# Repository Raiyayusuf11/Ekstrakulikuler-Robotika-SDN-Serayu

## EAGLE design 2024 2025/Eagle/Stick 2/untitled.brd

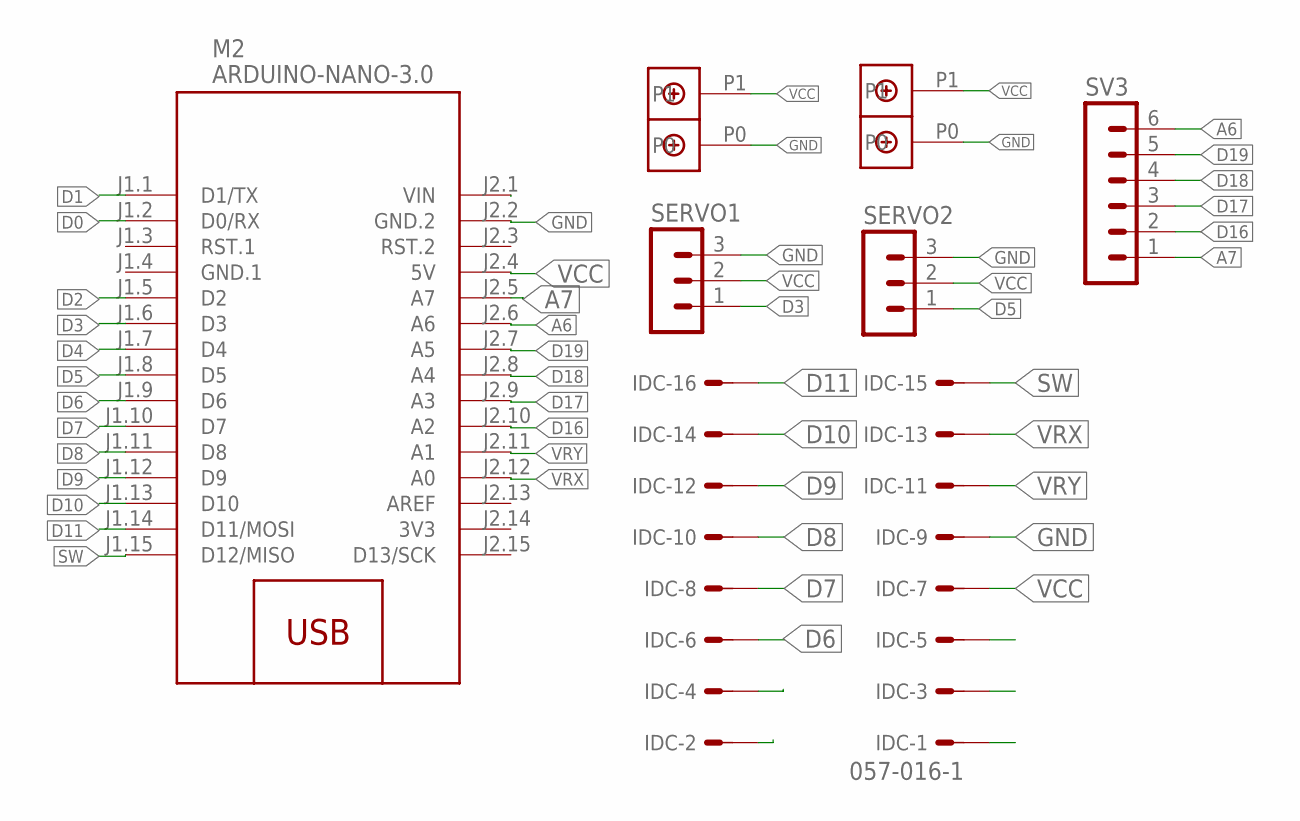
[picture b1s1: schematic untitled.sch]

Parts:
IDC: 057-016-1
M2: ARDUINO-NANO-3.0
SERVO1, SERVO2: MA03-1
SV3: MA06-1
U$1, U$2: DBCONN-1X2

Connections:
3V3: M2.J2.14 (3V3)
A6: M2.J2.6 (A6), SV3.6
A7: M2.J2.5 (A7), SV3.1
D: IDC.2, IDC.4
D0: M2.J1.2 (D0/RX)
D1: M2.J1.1 (D1/TX)
D2: M2.J1.5 (D2)
D3: M2.J1.6 (D3), SERVO1.1
D4: M2.J1.7 (D4)
D5: M2.J1.8 (D5), SERVO2.1
D6: IDC.6, M2.J1.9 (D6)
D7: IDC.8, M2.J1.10 (D7)
D8: IDC.10, M2.J1.11 (D8)
D9: IDC.12, M2.J1.12 (D9)
D10: IDC.14, M2.J1.13 (D10)
D11: IDC.16, M2.J1.14 (D11/MOSI)
D16: M2.J2.10 (A2), SV3.2
D17: M2.J2.9 (A3), SV3.3
D18: M2.J2.8 (A4), SV3.4
D19: M2.J2.7 (A5), SV3.5
GND: IDC.9, M2.J2.2 (GND.2), SERVO1.3, SERVO2.3, U$1.P0, U$2.P0
GND.1: M2.J1.4 (GND.1)
SW: IDC.15, M2.J1.15 (D12/MISO)
VCC: IDC.7, M2.J2.1 (VIN), M2.J2.4 (5V), SERVO1.2, SERVO2.2, U$1.P1, U$2.P1
VRX: IDC.13, M2.J2.12 (A0)
VRY: IDC.11, M2.J2.11 (A1)

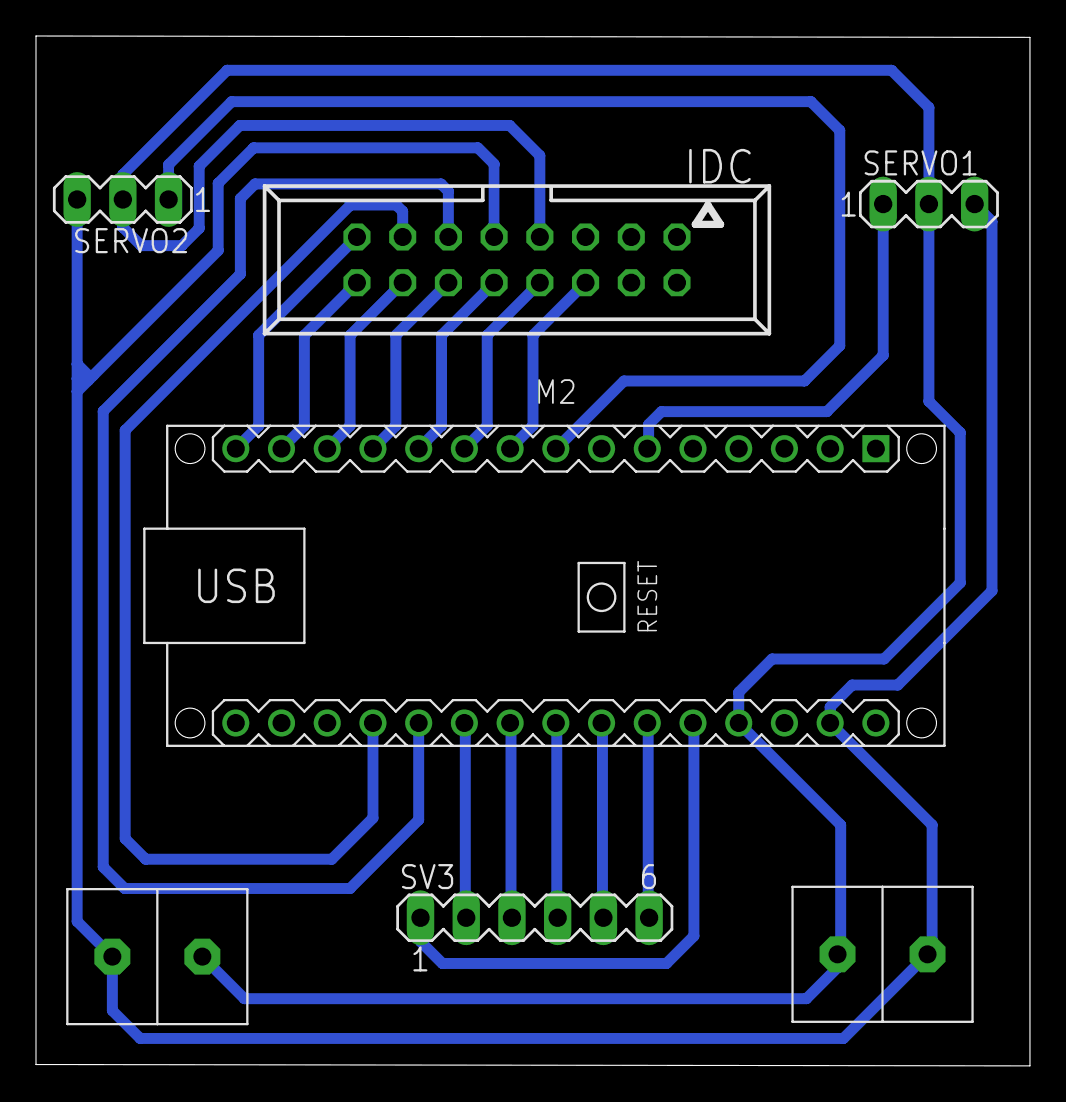
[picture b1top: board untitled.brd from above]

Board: 2 copper layers, 55.2 x 57.2 mm, 7 parts (0 on the bottom side), 20 nets.

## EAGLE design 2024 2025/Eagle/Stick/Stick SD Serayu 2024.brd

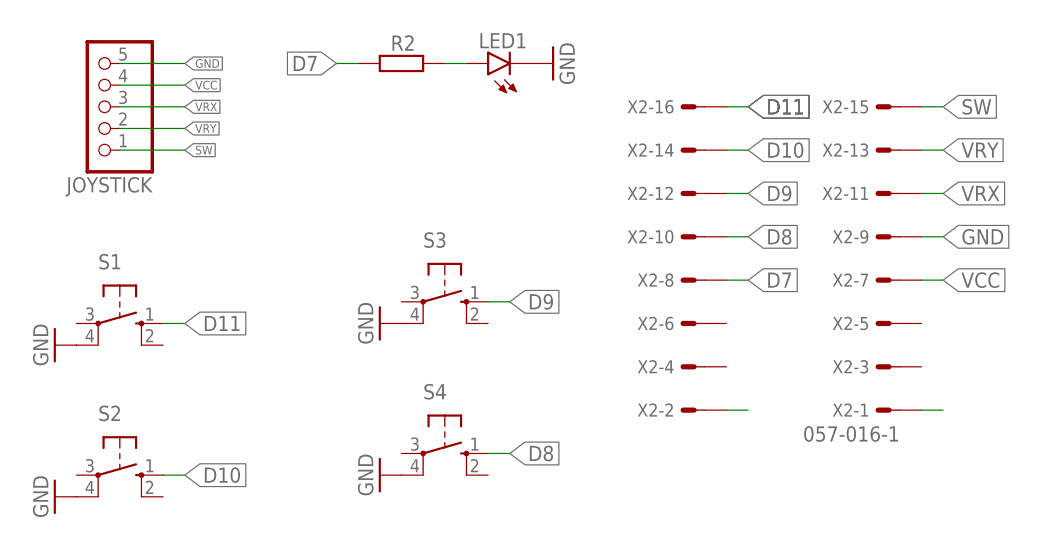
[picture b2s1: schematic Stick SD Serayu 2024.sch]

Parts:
JOYSTICK: PINHD-1X5; 1X05
LED1: LED5MM
R2: R-EU_R1206; R1206
S1, S2, S3, S4: 40-XX; B3F-40XX
X2: 057-016-1

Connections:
D7: R2.1, X2.8
D8: S4.1 (S), X2.10
D9: S3.1 (S), X2.12
D10: S2.1 (S), X2.14
D11: S1.1 (S), X2.16
GND: JOYSTICK.5, LED1.K (C), S1.4 (P1), S2.4 (P1), S3.4 (P1), S4.4 (P1), X2.9
unnamed: LED1.A, R2.2
SW: JOYSTICK.1, X2.15
VCC: JOYSTICK.4, X2.7
VRX: JOYSTICK.3, X2.11
VRY: JOYSTICK.2, X2.13

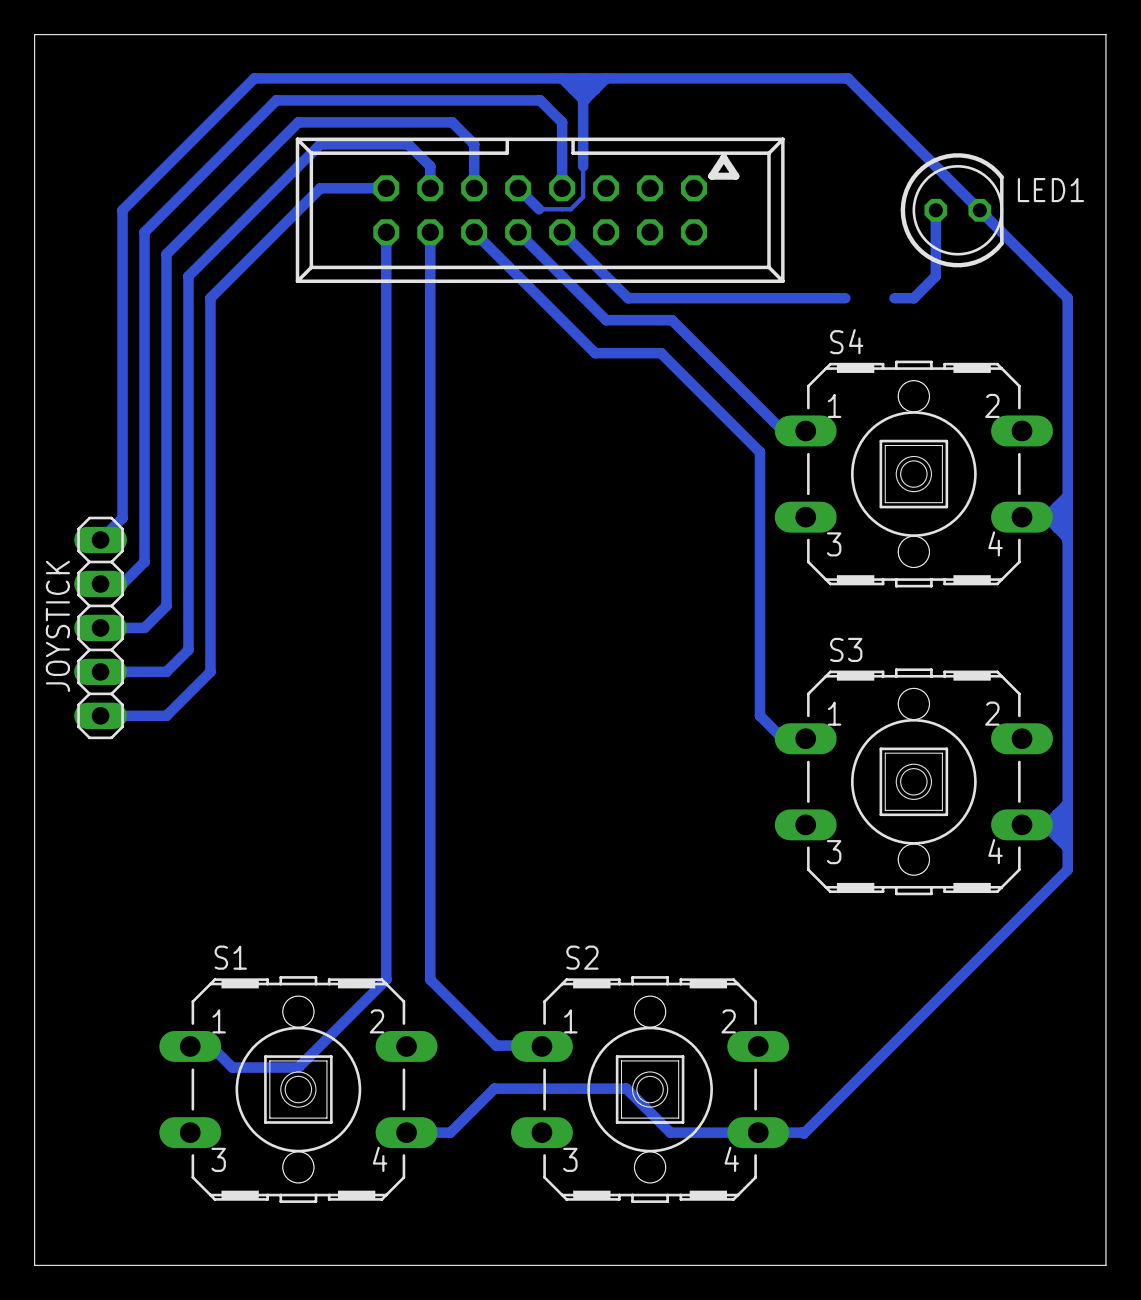
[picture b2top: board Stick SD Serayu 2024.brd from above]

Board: 2 copper layers, 61.9 x 71.1 mm, 8 parts (1 on the bottom side), 11 nets.

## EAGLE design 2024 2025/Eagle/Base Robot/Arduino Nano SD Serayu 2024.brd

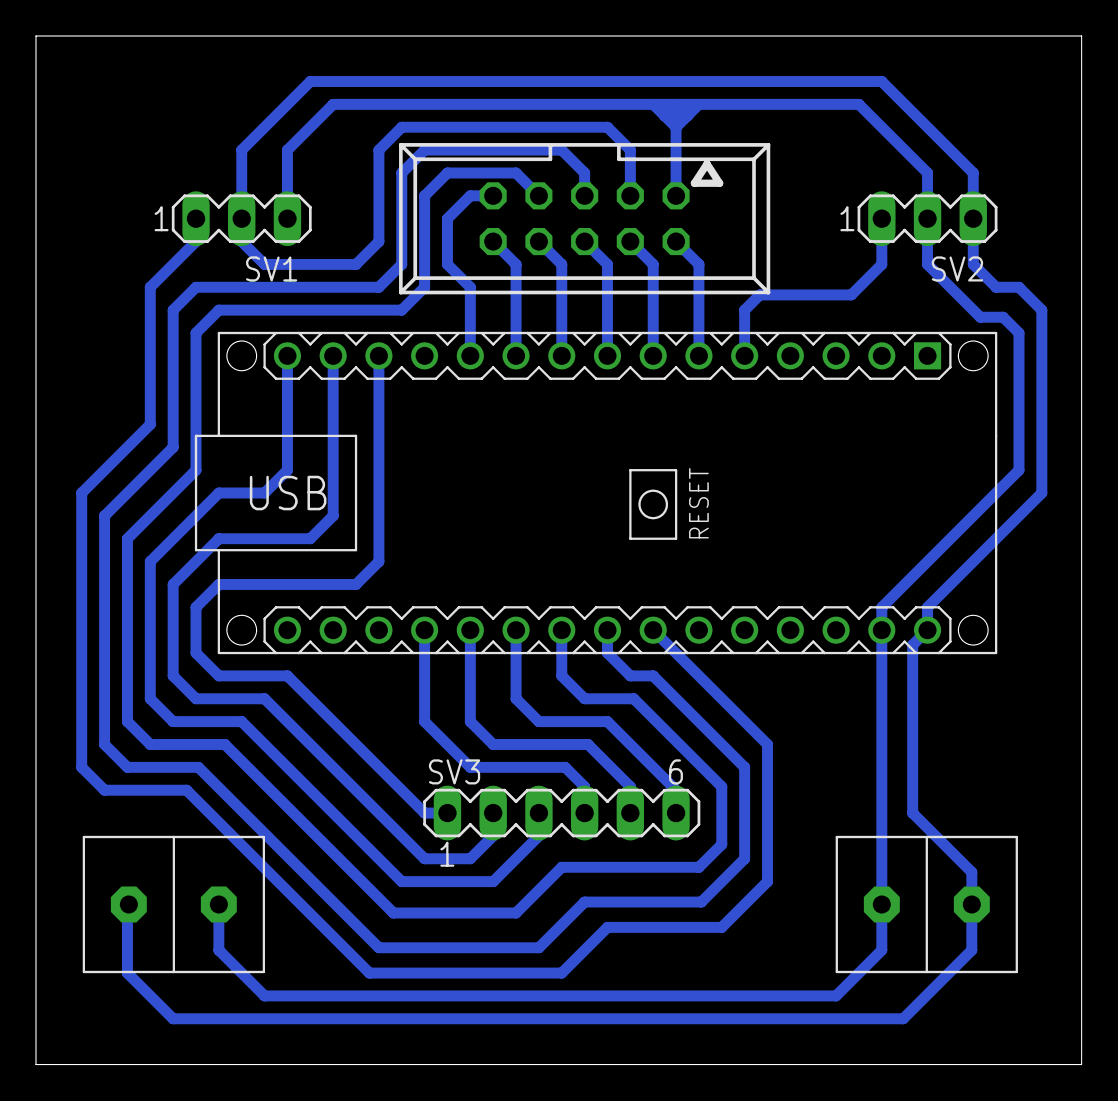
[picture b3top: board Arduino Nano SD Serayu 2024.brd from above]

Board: 2 copper layers, 58.1 x 57.1 mm, 7 parts (0 on the bottom side), 18 nets.

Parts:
M2: ARDUINO-NANO-3.0
SV1, SV2: MA03-1
SV3: MA06-1
U$1, U$2: DBCONN-1X2
X1: 057-010-1

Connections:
A3: M2.J2.9, X1.7
A4: M2.J2.8, X1.5
D2: M2.J1.5, SV2.1
D3: M2.J1.6, X1.2
D4: M2.J1.7, X1.4
D5: M2.J1.8, X1.6
D6: M2.J1.9, X1.8
D7: M2.J1.10, X1.10
D8: M2.J1.11, X1.9
D10: M2.J1.13, SV3.1
D11: M2.J1.14, SV3.2
D12: M2.J1.15, SV3.3
D14: M2.J2.12, SV3.4
D15: M2.J2.11, SV3.5
D16: M2.J2.10, SV3.6
D19: M2.J2.7, SV1.1
GND: M2.J2.2, SV1.3, SV2.2, U$1.P0, U$2.P0, X1.1
VCC: M2.J2.1, SV1.2, SV2.3, U$1.P1, U$2.P1, X1.3

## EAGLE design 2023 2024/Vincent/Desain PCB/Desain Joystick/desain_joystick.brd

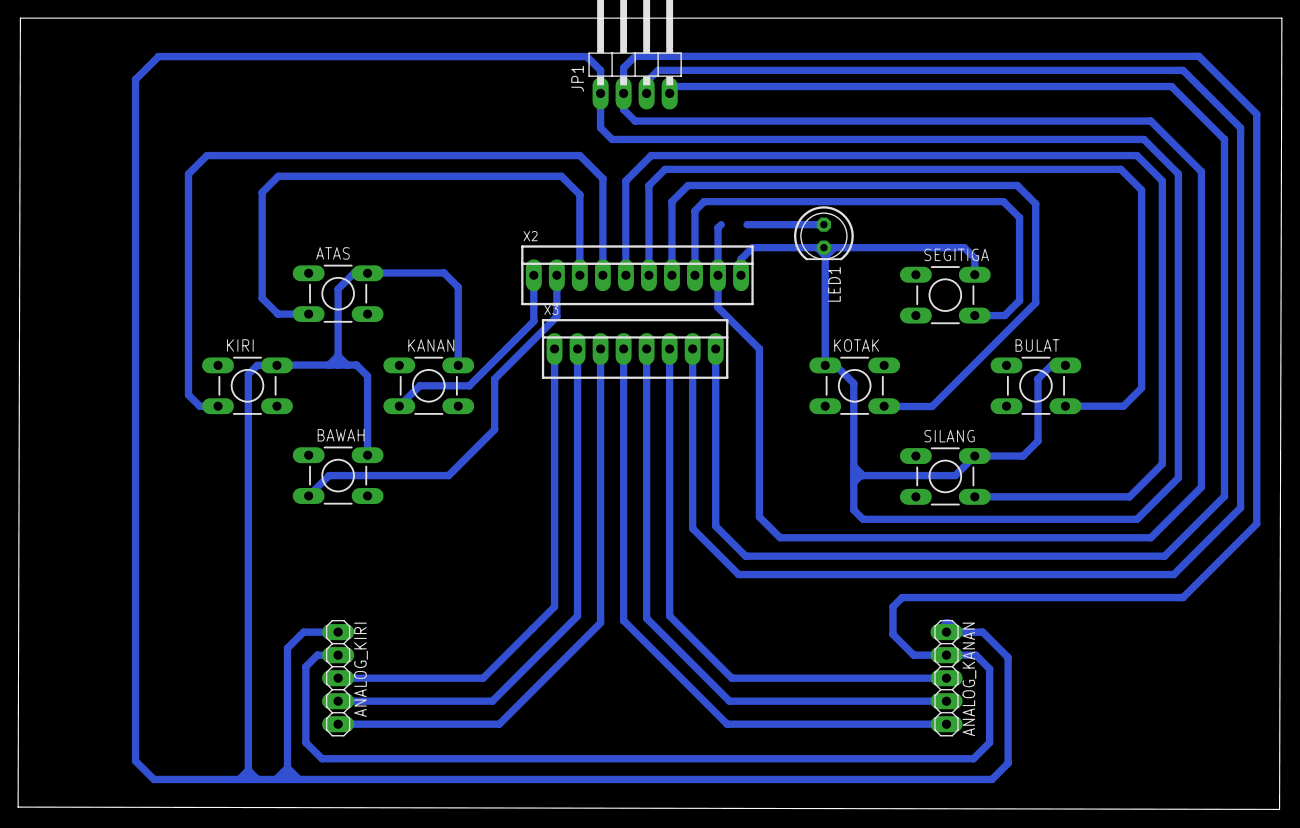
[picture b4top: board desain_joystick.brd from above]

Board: 2 copper layers, 139.4 x 87.3 mm, 15 parts (1 on the bottom side), 19 nets.

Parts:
ANALOG_KANAN: 1X05
ANALOG_KIRI: 1X05
ATAS: DTS-6
BAWAH: DTS-6
BULAT: DTS-6
JP1: 1X04/90
KANAN: DTS-6
KIRI: DTS-6
KOTAK: DTS-6
LED1: LED5MM
R2: R1206
SEGITIGA: DTS-6
SILANG: DTS-6
X2: 22-23-2101
X3: 22-23-2081

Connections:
ATAS: ATAS.3, X2.3
BAWAH: BAWAH.3, X2.2
BULAT: BULAT.4, X2.6
GND: ANALOG_KANAN.1, ANALOG_KIRI.1, ATAS.2, BAWAH.2, BULAT.2, JP1.1, KANAN.2, KIRI.2, KOTAK.1, LED1.K, SEGITIGA.2, SILANG.2, X2.10
KANAN: KANAN.3, X2.1
KIRI: KIRI.3, X2.4
KOTAK: KOTAK.4, X2.7
unnamed: LED1.A, R2.2
SCL: JP1.3, X3.7
SDA: JP1.4, X3.8
SEGITIGA: SEGITIGA.4, X2.8
SILANG: SILANG.4, X2.5
SW1: ANALOG_KIRI.5, X3.3
SW2: ANALOG_KANAN.5, X3.4
VCC: ANALOG_KANAN.2, ANALOG_KIRI.2, JP1.2, R2.1, X2.9
VRX1: ANALOG_KIRI.3, X3.1
VRX2: ANALOG_KANAN.3, X3.6
VRY1: ANALOG_KIRI.4, X3.2
VRY2: ANALOG_KANAN.4, X3.5

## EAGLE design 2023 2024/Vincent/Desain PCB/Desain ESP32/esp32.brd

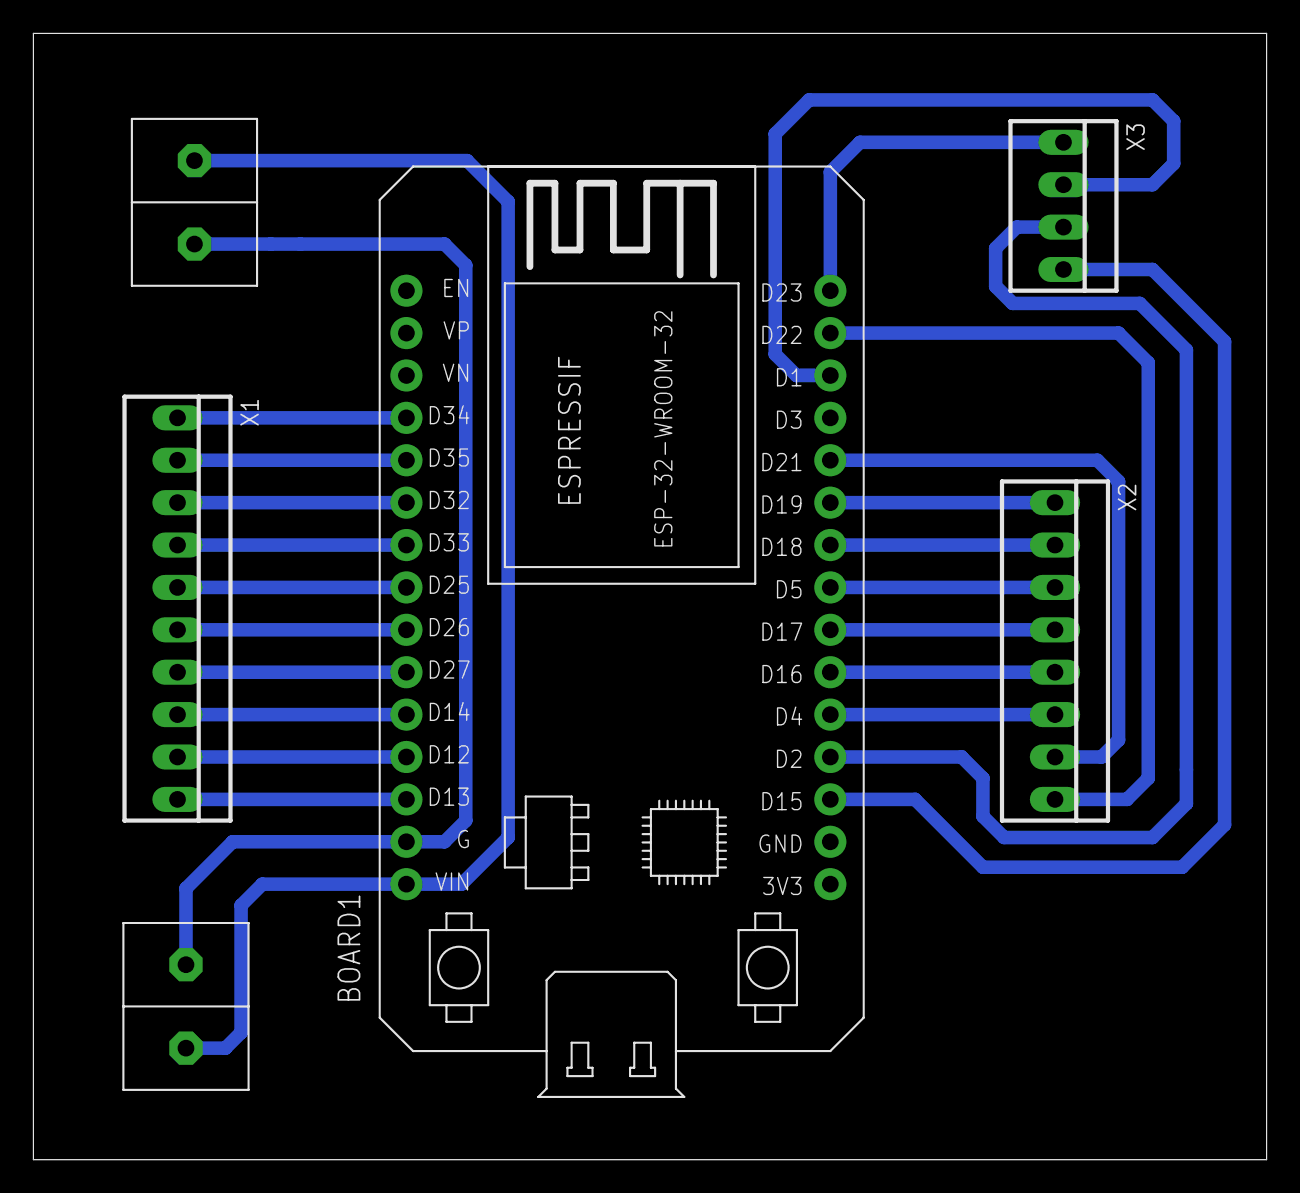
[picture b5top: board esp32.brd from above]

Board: 2 copper layers, 73.9 x 67.5 mm, 6 parts (0 on the bottom side), 24 nets.

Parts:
BOARD1: ESP32DEVKITV1; ESP32-DEVKITV1
U$1, U$2: DBCONN-1X2
X1: 22-23-2101
X2: 22-23-2081
X3: 22-23-2041

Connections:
D1: BOARD1.D1, X3.2
D2: BOARD1.D2, X3.3
D4: BOARD1.D4, X2.6
D5: BOARD1.D5, X2.3
D12: BOARD1.D12, X1.9
D13: BOARD1.D13, X1.10
D14: BOARD1.D14, X1.8
D15: BOARD1.D15, X3.4
D16: BOARD1.D16, X2.5
D17: BOARD1.D17, X2.4
D18: BOARD1.D18, X2.2
D19: BOARD1.D19, X2.1
D23: BOARD1.D23, X3.1
D25: BOARD1.D25, X1.5
D26: BOARD1.D26, X1.6
D27: BOARD1.D27, X1.7
D32: BOARD1.D32, X1.3
D33: BOARD1.D33, X1.4
D34: BOARD1.D34, X1.1
D35: BOARD1.D35, X1.2
GND: BOARD1.GND, U$1.P0, U$2.P0
SCL: BOARD1.D22, X2.8
SDA: BOARD1.D21, X2.7
VCC: BOARD1.VIN, U$1.P1, U$2.P1

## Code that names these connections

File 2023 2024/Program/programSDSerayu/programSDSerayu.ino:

#include <Adafruit_SSD1306.h>
#include <splash.h>

#include <Adafruit_GFX.h>
#include <Adafruit_GrayOLED.h>
#include <Adafruit_SPITFT.h>
#include <Adafruit_SPITFT_Macros.h>
#include <gfxfont.h>




// ------------------------------------initialization pins
// joystick (pin -> kiri|kanan)
int pinVrx[2] = {19, 4};
int pinVry[2] = {18, 16};
int pinSw[2] = {5, 17};

// button
int pinButton[8] = {12, 13, 14, 25, 26, 27, 32, 33};

// oled
int pinSda = 21, pinScl = 22;

// driver motor
int pinMotor[4] = {15, 2, 1, 23};
// int pinMotor1 = 15, pinMotor2 = 2;
// int pinMotor3 = 1, pinMotor4 = 23;

// ------------------------------------variables
// joystick
int nilaiXkiri, nilaiYkiri, nilaiSwkiri;
int nilaiXkanan, nilaiYkanan, nilaiSwkanan;

// oled
const int lebar = 128;
const int tinggi = 64;
const int reset = 4;

Adafruit_SSD1306 oled(lebar, tinggi, &Wire, reset);

void cekButton() {
  const char* buttonName[] = {"Bawah", "Kanan", "Atas", "Bulat", "Silang", "Kiri", "Segitiga", "Kotak"};

  for(int i = 0; i < 8; i++) {
    if(digitalRead(pinButton[i]) == HIGH) Serial.println(buttonName[i]);
  }
}

int test = 0;

void setup() {
  Serial.begin(9600);
  Serial.print("Ready bang!");

  for(int i = 0; i < 2; i++) {
   pinMode(pinVrx[i], INPUT); 
   pinMode(pinVry[i], INPUT);
   pinMode(pinSw[i], INPUT_PULLUP);
  }

  for(int i = 0; i < 8; i++) {
    pinMode(pinButton[i], INPUT_PULLUP);
  }

  // pinMode(pinSda, INPUT); 
  // pinMode(pinScl, INPUT);

  for(int i = 0; i < 4; i++) {
    pinMode(pinMotor[i], OUTPUT);
  }

  oled.begin(SSD1306_SWITCHCAPVCC, 0x3C);
  oled.clearDisplay();
  
}

void loop() {
  CekJoystick();
  // CekButton();
  MovementRobot();

  if (digitalRead(pinButton[0]) == LOW) {
    Serial.println("nyala");
  } else {
    Serial.println("Mati");
  }
  
  // oled.setTextSize(2);
  // oled.setTextColor(WHITE);
  // oled.setCursor(12, 15);
  // oled.println("Test");
  // oled.display();

  delay(100);
}


void CekButton() {
  if (digitalRead(pinButton[0]) == HIGH) {
    Serial.println("Bawah");
  }
  // if (digitalRead(pinButton[1]) == HIGH) {
  //   Serial.println("Kanan");
  // }
  // if (digitalRead(pinButton[2]) == HIGH) {
  //   Serial.println("Kiri");
  // }
  // if (digitalRead(pinButton[3]) == HIGH) {
  //   Serial.println("Bulat");
  // }
  // if (digitalRead(pinButton[4]) == HIGH) {
  //   Serial.println("Silang");
  // }
  // if (digitalRead(pinButton[5]) == HIGH) {
  //   Serial.println("Kotak");
  // }
  // if (digitalRead(pinButton[6]) == HIGH) {
  //   Serial.println("Segitiga");
  // }
  // if (digitalRead(pinButton[7]) == HIGH) {
  //   Serial.println("Atas");
  // }
}

void CekJoystick() {
  nilaiXkiri = map(analogRead(pinVrx[0]), 0, 1023, 0, 180);
  nilaiYkiri = map(analogRead(pinVry[0]), 0, 1023, 0, 180);
  nilaiSwkiri = digitalRead(pinSw[0]);

  nilaiXkanan = map(analogRead(pinVrx[1]), 0, 1023, 0, 180);
  nilaiYkanan = map(analogRead(pinVry[1]), 0, 1023, 0, 180);
  nilaiSwkanan = digitalRead(pinSw[1]);

  Serial.print("X2 : "); Serial.print(nilaiXkanan);
  Serial.print(" Y2 : "); Serial.print(nilaiYkanan);
  Serial.print(" SW2 : "); Serial.print(nilaiSwkanan);

  Serial.print(" X1 : "); Serial.print(nilaiXkiri);
  Serial.print(" Y1 : "); Serial.print(nilaiYkiri);
  Serial.print(" SW1 : "); Serial.print(nilaiSwkiri);

  if (nilaiXkanan == 720 && nilaiYkanan == 0) {
    Serial.print(" Kanan");
  } else if (nilaiXkanan == 0 && nilaiYkanan == 0) {
    Serial.print(" Kiri");
  }else if (nilaiSwkanan == 0) {
    Serial.print(" R3");
  }

  // if (nilaiXKiri == 720 && nilaiYkanan == 0) {
  //   Serial.print(" Kanan");
  // } else if (nilaiXkanan == 0 && nilaiYkanan == 0) {
  //   Serial.print(" Kiri");
  // }else if (nilaiSwkanan == 0) {
  //   Serial.print(" R3");
  // }

  Serial.println();
  delay(100);

}

void SetMotor(int motor1, int motor2, int motor3, int motor4) {
  digitalWrite(pinMotor[0], motor1); 
  digitalWrite(pinMotor[1], motor2);
  digitalWrite(pinMotor[2], motor4);
  digitalWrite(pinMotor[3], motor3);
}

void MovementRobot() {
  if(nilaiXkanan == 720 && nilaiYkanan == 0) {
    SetMotor(0,0,0,1);
  } else if(nilaiXkanan == 0 && nilaiYkanan == 0) {
    SetMotor(1,0,0,0);
  } else if (nilaiSwkanan == 0) {
    SetMotor(0,1,1,0);
    Serial.print("Maju");
  } else if (nilaiSwkiri == 0) {
    SetMotor(1,0,0,1);
    Serial.print("Mundur");
  }

  // if(nilaiXkanan == 720 && nilaiYkanan == 0) {
  //   SetMotor(0,0,0,1);
  // } else if(nilaiXkanan == 0 && nilaiYkanan == 0) {
  //   SetMotor(1,0,0,0);
  // } else if (nilaiSwkanan == 0) {
  //   SetMotor(0,1,1,0);
  //   Serial.print("Maju");
  // } else if (nilaiSwkiri == 0) {
  //   SetMotor(1,0,0,1);
  //   Serial.print("Mundur");
  // }
  
  // else if(nilaiXkiri == 720 && nilaiYkiri == 0) {
  //   SetMotor(1,0,0,0);
  // } else if(nilaiXkiri == 0 && nilaiYkiri == 0) {
  //   SetMotor(0,0,1,0);
  // } else if (nilaiSwkiri == 0) {
  //   SetMotor(1,0,1,0);
  // } 
  
  else {
    SetMotor(0,0,0,0);
  }
  delay(200);
}

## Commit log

2024-09-30 first init github sinchan

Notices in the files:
parts and their libraries:
diy-modules: Released under the Creative Commons Attribution 4.0 International License: http://creativecommons.org/licenses/by/4.0
